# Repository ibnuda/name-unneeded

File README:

Name Unneeded
36 keys, your basic minidox-look-alike.
38 keys, your basic minidox-look-alike plus 2 more thumb keys.

both drawing can be used with or without kaihua's hotswap socket.

Firmware
both model uses ibnuda/squiggle's firmware.
specifically, 3x5_3 and thumbrow layout.

Notes:
pimoroni's footprint is made by either @bomtarnes or @davidphilipbarr.

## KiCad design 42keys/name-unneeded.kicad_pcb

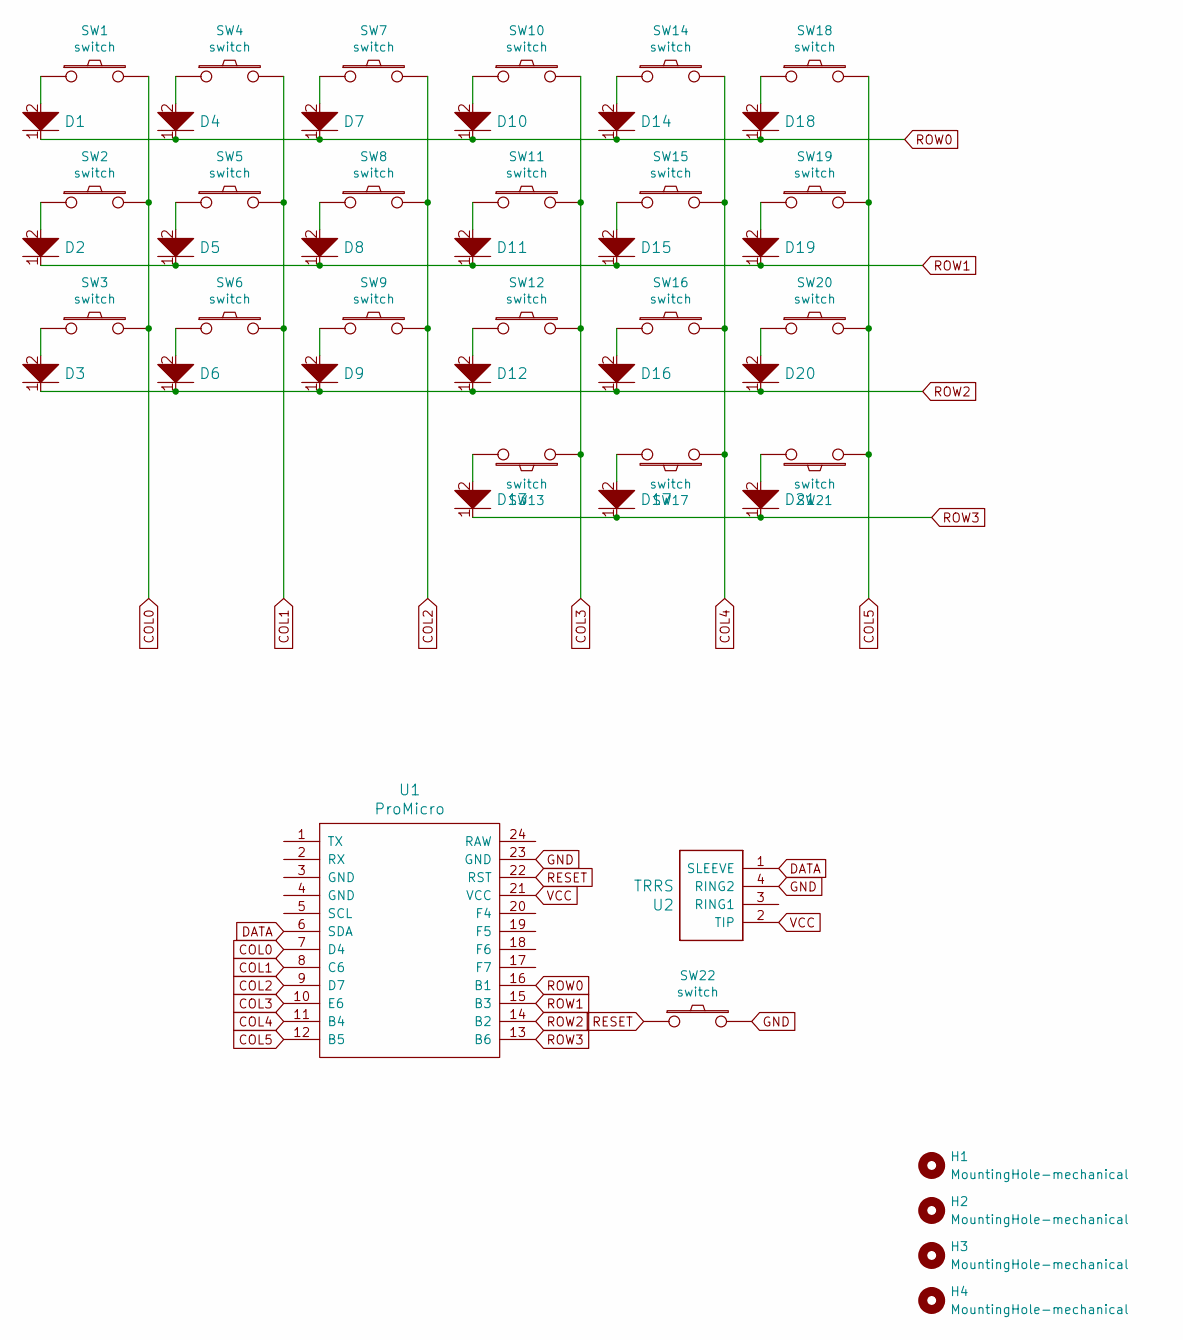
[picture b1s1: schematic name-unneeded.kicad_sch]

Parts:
D1, D2, D3, D4, D5, D6, D7, D8, D9, D10, D11, D12, D13, D14, D15, D16, D17, D18, D19, D20, D21: D; diode-smd-tht
H1, H2, H3, H4: MountingHole-mechanical; hole-m2-pcb
SW1, SW2, SW3, SW4, SW5, SW6, SW7, SW8, SW9, SW10, SW11, SW12, SW13, SW14, SW15, SW16, SW17, SW18, SW19, SW20, SW21: switch; choc-socket-flip
SW22: switch; reset
U1: ProMicro; promicro
U2: TRRS; trrs

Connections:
COL0: SW1.2, SW2.2, SW3.2, U1.7 (D4)
COL1: SW4.2, SW5.2, SW6.2, U1.8 (C6)
COL2: SW7.2, SW8.2, SW9.2, U1.9 (D7)
COL3: SW10.2, SW11.2, SW12.2, SW13.1, U1.10 (E6)
COL4: SW14.2, SW15.2, SW16.2, SW17.1, U1.11 (B4)
COL5: SW18.2, SW19.2, SW20.2, SW21.1, U1.12 (B5)
DATA: U1.6 (SDA), U2.1 (SLEEVE)
GND: SW22.2, U1.23 (GND), U2.4 (RING2)
unnamed: D1.2, SW1.1
unnamed: D2.2, SW2.1
unnamed: D3.2, SW3.1
unnamed: D4.2, SW4.1
unnamed: D5.2, SW5.1
unnamed: D6.2, SW6.1
unnamed: D7.2, SW7.1
unnamed: D8.2, SW8.1
unnamed: D9.2, SW9.1
unnamed: D10.2, SW10.1
unnamed: D11.2, SW11.1
unnamed: D12.2, SW12.1
unnamed: D13.2, SW13.2
unnamed: D14.2, SW14.1
unnamed: D15.2, SW15.1
unnamed: D16.2, SW16.1
unnamed: D17.2, SW17.2
unnamed: D18.2, SW18.1
unnamed: D19.2, SW19.1
unnamed: D20.2, SW20.1
unnamed: D21.2, SW21.2
RESET: SW22.1, U1.22 (RST)
ROW0: D1.1, D4.1, D7.1, D10.1, D14.1, D18.1, U1.16 (B1)
ROW1: D2.1, D5.1, D8.1, D11.1, D15.1, D19.1, U1.15 (B3)
ROW2: D3.1, D6.1, D9.1, D12.1, D16.1, D20.1, U1.14 (B2)
ROW3: D13.1, D17.1, D21.1, U1.13 (B6)
VCC: U1.21 (VCC), U2.2 (TIP)

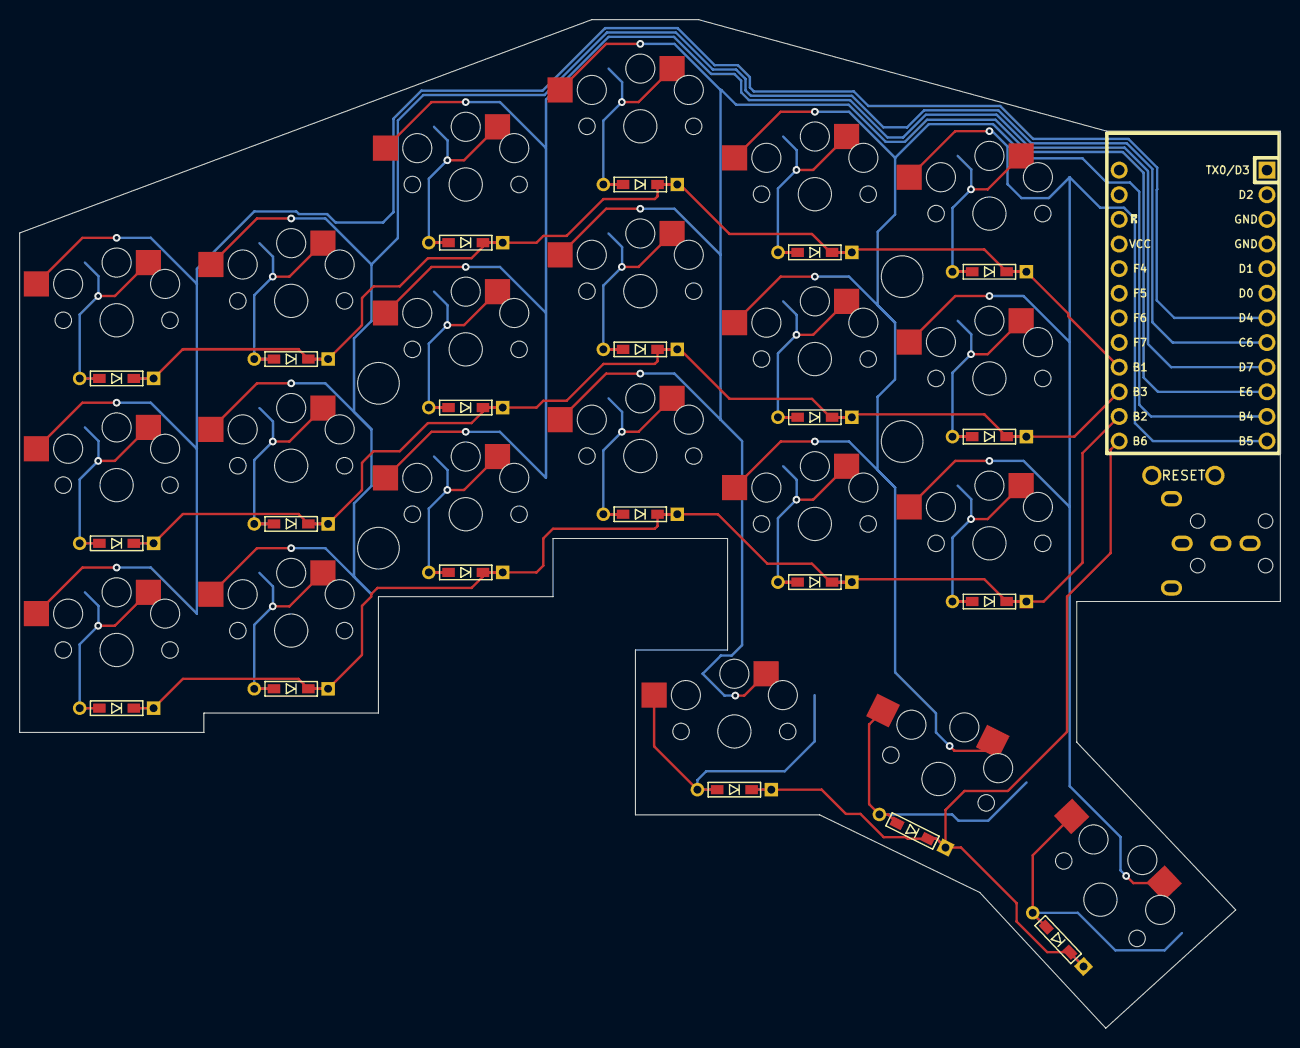
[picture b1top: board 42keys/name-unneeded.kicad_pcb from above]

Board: 2 copper layers, 130.0 x 104.0 mm, 49 parts (1 on the bottom side), 35 nets.

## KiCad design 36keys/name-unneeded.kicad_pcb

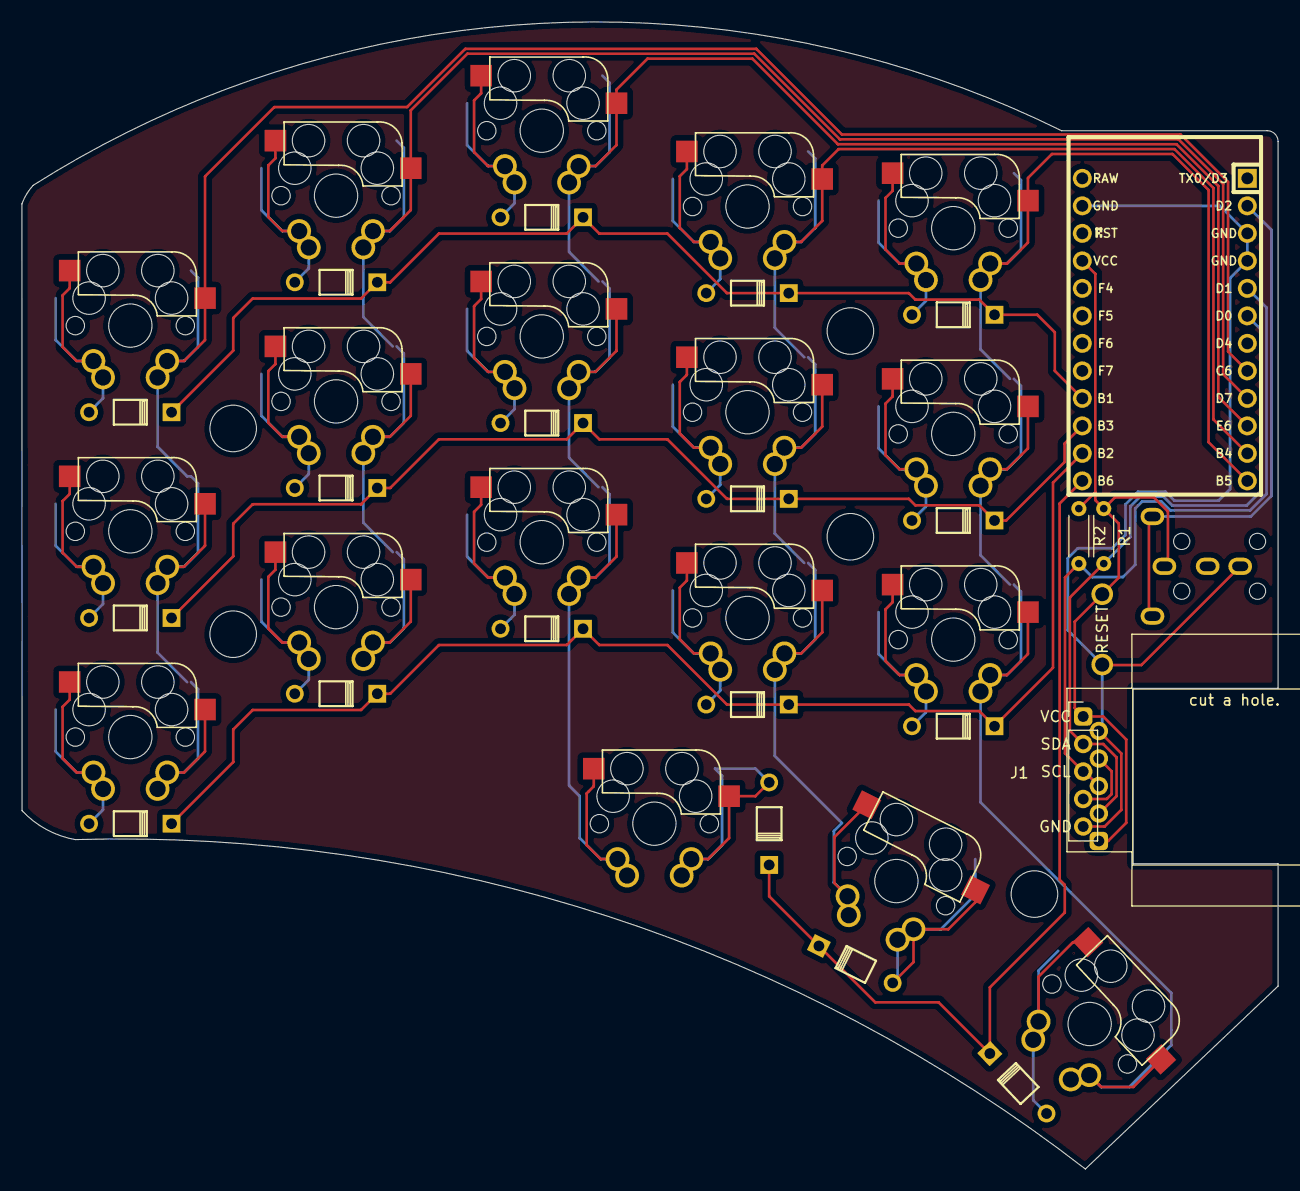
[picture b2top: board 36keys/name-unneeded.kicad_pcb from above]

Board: 2 copper layers, 116.0 x 105.9 mm, 47 parts (1 on the bottom side), 32 nets.

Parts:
D1, D2, D3, D4, D5, D6, D7, D8, D9, D10, D11, D12, D13, D14, D15, D16, D17, D18: D; diode
H1, H2, H3, H4, H5: MountingHole; hole-m2-pcb
J1: Conn_01x05; pimoroni-trackball-reversible
R1, R2: R; R_Axial_DIN0204_L3.6mm_D1.6mm_P5.08mm_Horizontal
SW1, SW2, SW3, SW4, SW5, SW6, SW7, SW8, SW9, SW10, SW11, SW12, SW13, SW14, SW16, SW17, SW18, SW19: switch; 1u-dual-socket
SW15: switch; reset
U1: ProMicro; promicro
U2: TRRS; trrs

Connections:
COL0: SW1.2, SW2.2, SW3.2, U1.8
COL1: SW4.2, SW5.2, SW6.2, U1.9
COL2: SW7.2, SW8.2, SW9.2, SW10.1, U1.10
COL3: SW11.2, SW12.2, SW13.2, SW14.1, U1.11
COL4: SW16.2, SW17.2, SW18.2, SW19.2, U1.12
DATA: U1.2, U2.1
GND: J1.5, SW15.2, U1.3, U1.4, U1.23, U2.4
unnamed: D1.2, SW1.1
unnamed: D2.2, SW2.1
unnamed: D3.2, SW3.1
unnamed: D4.2, SW4.1
unnamed: D5.2, SW5.1
unnamed: D6.2, SW6.1
unnamed: D7.2, SW7.1
unnamed: D8.2, SW8.1
unnamed: D9.2, SW9.1
unnamed: D10.2, SW10.2
unnamed: D11.2, SW11.1
unnamed: D12.2, SW12.1
unnamed: D13.2, SW13.1
unnamed: D14.2, SW14.2
unnamed: D15.2, SW16.1
unnamed: D16.2, SW17.1
unnamed: D17.2, SW18.1
unnamed: D18.2, SW19.1
ROW0: D1.1, D4.1, D7.1, D11.1, D15.1, U1.16
ROW1: D2.1, D5.1, D8.1, D12.1, D16.1, U1.15
ROW2: D3.1, D6.1, D9.1, D13.1, D17.1, U1.14
ROW3: D10.1, D14.1, D18.1, U1.13
SCL: J1.3, R2.2, U1.5
SDA: J1.2, R1.2, U1.6
VCC: J1.1, R1.1, R2.1, SW15.1, U1.21, U2.2

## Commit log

2020-12-21 36 keys.
2020-12-21 38 keys.
2020-12-21 readme.
2020-12-21 deleted link.
2020-12-21 images.
2020-12-21 removed stray lines from kicad export of the edge-cuts.
2020-12-21 removed backup file from librecad.
2021-01-04 shell case.
2021-01-04 license and readme.
2021-01-04 readme
2021-01-10 added pimoroni's footprint.
2021-03-02 34 weird.
2022-08-28 whatever.
